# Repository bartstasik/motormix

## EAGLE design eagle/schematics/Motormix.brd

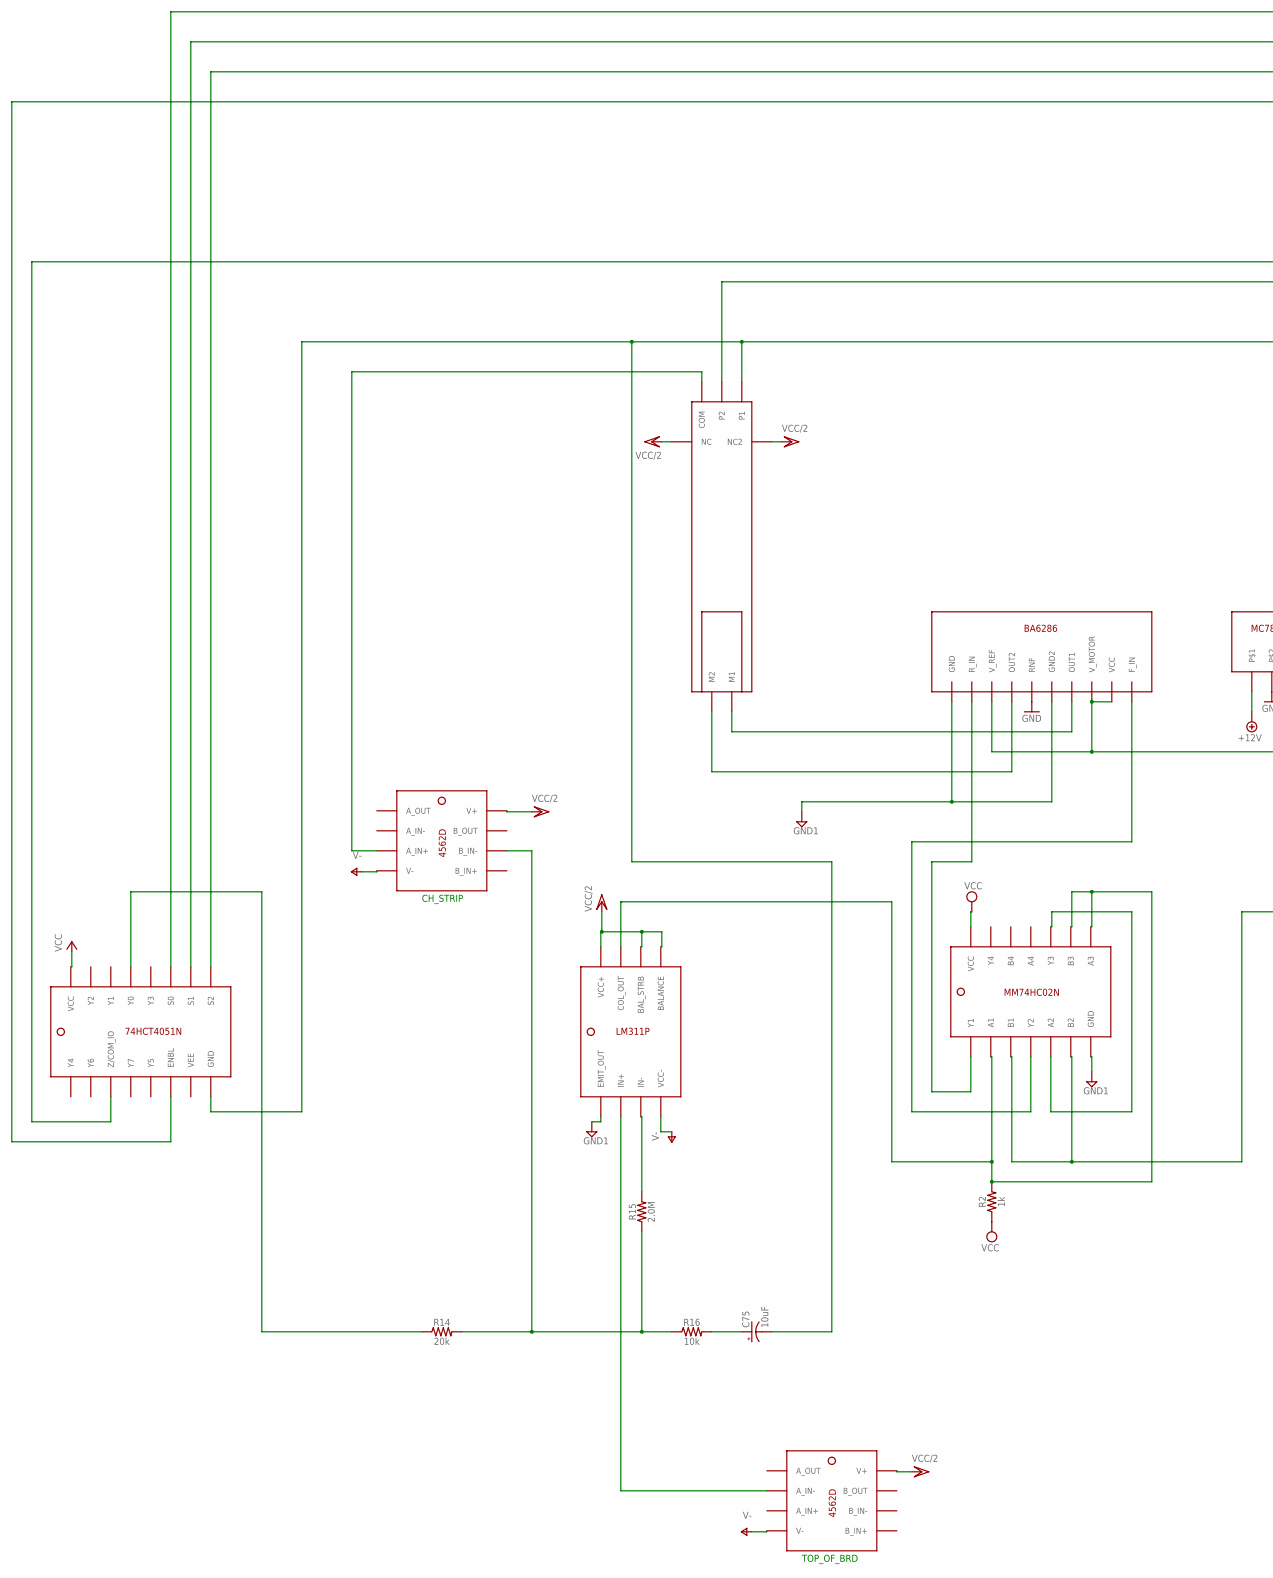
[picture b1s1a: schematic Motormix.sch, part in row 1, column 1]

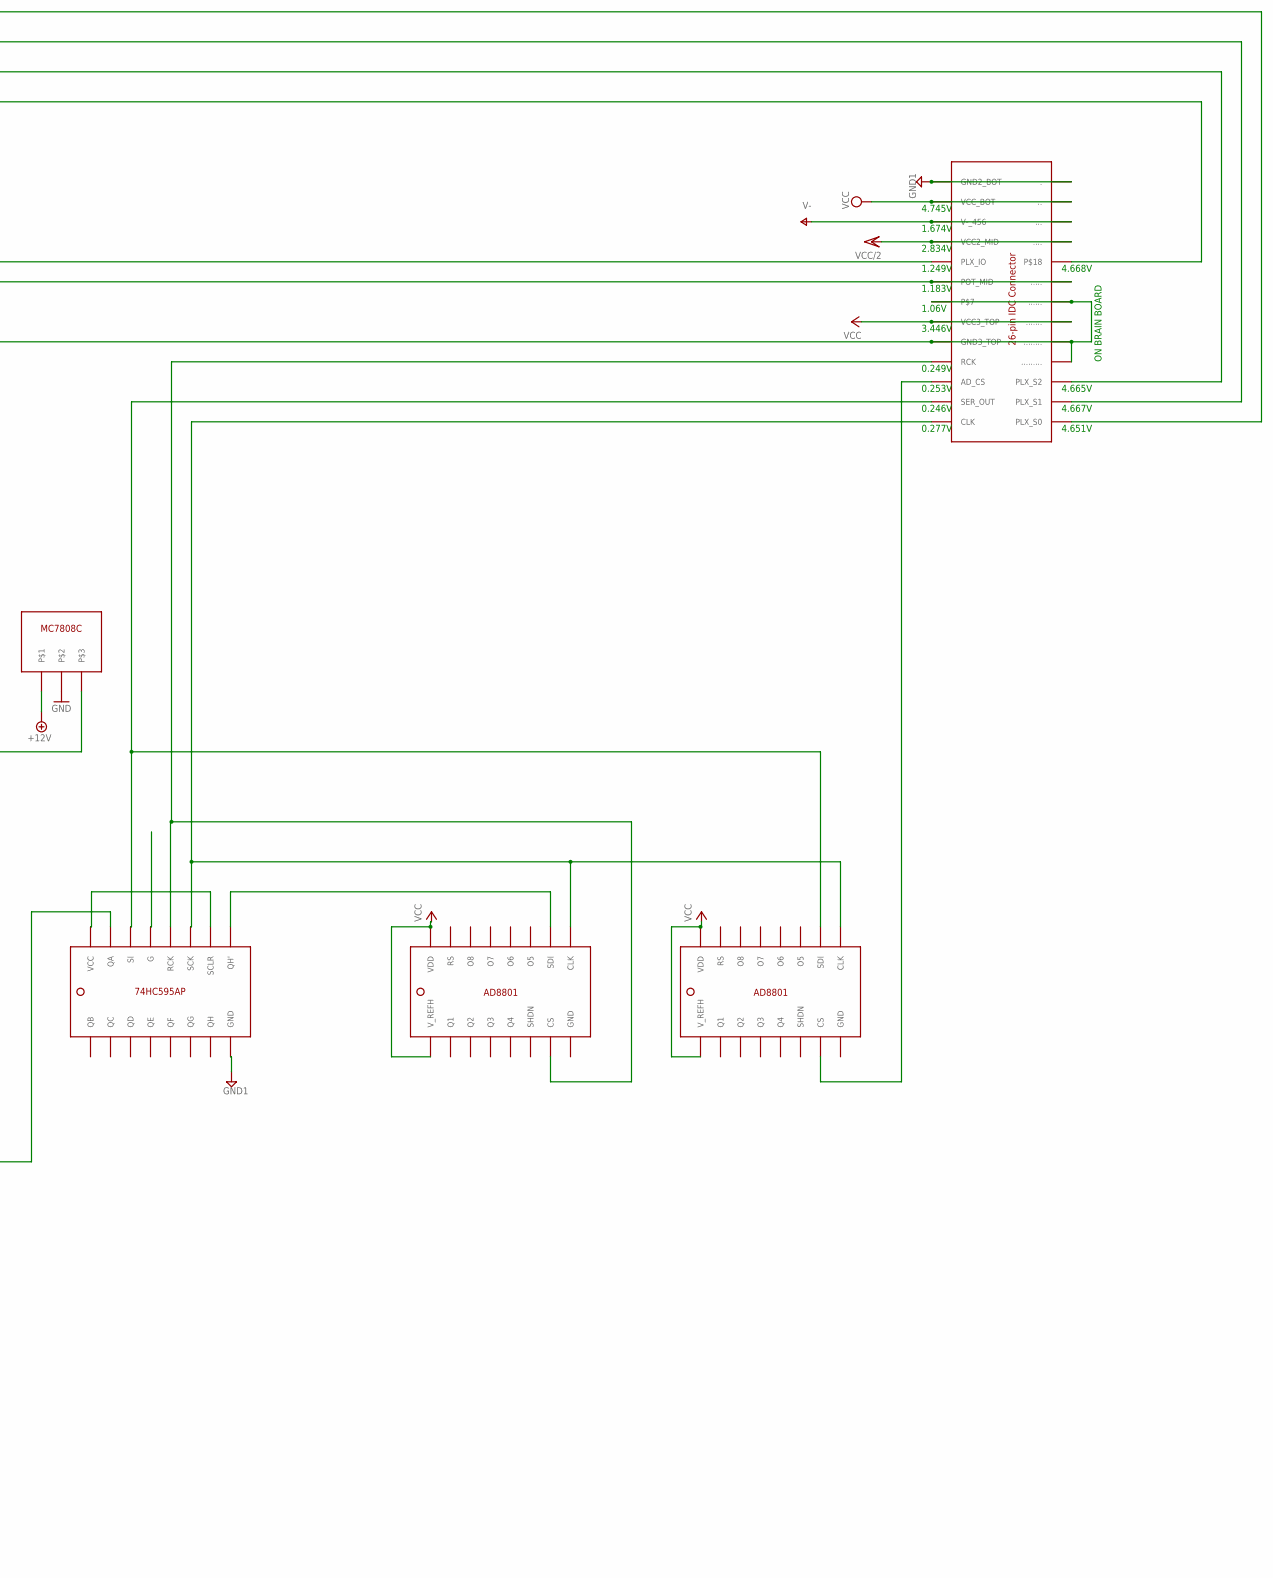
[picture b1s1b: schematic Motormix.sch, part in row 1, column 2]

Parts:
C75: 10uF; CPOL-RADIAL-2.5MM-5MM
R2: 1k; AXIAL-0.3
R14: 20k; 0603
R15: 2.0M; 0603
R16: 10k; 0603

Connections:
unnamed: R14.2, R15.1, R16.1
unnamed: C75.1 (+), R16.2
VCC: R2.P$1 (1)

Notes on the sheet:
ON BRAIN BOARD
0.249V
0.253V
0.246V
0.277V
4.665V
4.667V
4.651V
4.745V
1.674V
2.834V
1.249V
1.183V
1.06V
3.446V
4.668V
CH_STRIP
TOP_OF_BRD

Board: 2 copper layers, 5 parts (0 on the bottom side), 2 nets, no tracks yet.

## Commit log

2023-06-11 eagle: add schematic and library of Motormix
    To try and understand how to move the motors on the motor board, follow
    the traces on it and make a basic schematic.
2023-06-27 pico-mp: write some basic code to test Motormix
    Write some code to test the 595 shift register and the 4051 multiplexer.
    The shift register works as expected, but the multiplexer behaves
    unpredictably. Dropping this until later.
2023-06-27 pico-mp: write multiple tests to figure fader control
    Tinker with the faders, with the goal of having great control of moving
    them wherever.
    Write some test code to make it follow a separate potentiometer.
    Write some test code to make it go to hardcoded positions.
    Implement a proportional (P) motor controller, as a start for
    implementing a PID controller (probably unnecessary here, but will be a
2023-06-27 gitignore: add from template
2023-06-27 midi: figure out Kronos data
2023-06-27 hui: upload docs found online
2023-06-27 midi: send hardcoded data from Pico to Kronos
2023-06-27 midi: add more Kronos controls
2023-06-27 midi: ctrl Kronos timbre vol. with physical fader
2023-06-27 pico: clarify directory structure
2023-06-27 midi: encapsulate KronosMessage
2023-06-27 midi: add old code.py under new name
2023-06-27 gitignore: add for pico folder
2023-06-27 pico-mp: fix minor typo and add test_pot test
2023-06-27 pico-cp: port motor code from MicroPython pico_mp
2023-06-27 midi: slightly modify the test
2023-06-27 pico-cp: link Kronos fader with the motorised one
    Move ported motor-movement code to a separate file for future reference.
    Slightly modify the `KronosMessage` parser to stop parsing if a MIDI
    packet is empty (prevent it getting stuck in the loop when it receives
    any other data).
    Receive and parse Kronos fader-movement data, and make the motorised
    fader move to that position.

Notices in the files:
parts and their libraries:
SparkFun-Resistors: Licensing: Creative Commons ShareAlike 4.0 International - https://creativecommons.org/licenses/by-sa/4.0
